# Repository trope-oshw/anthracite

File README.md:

[日本語](README.ja.md)

# Anthracite

**Schematics**
- In the browser (KiCanvas): [top](https://kicanvas.org/?repo=https%3A%2F%2Fgithub.com%2Ftrope-oshw%2Fanthracite%2Ftree%2Fmain%2Fhardware%2Ftop), [bottom](https://kicanvas.org/?repo=https%3A%2F%2Fgithub.com%2Ftrope-oshw%2Fanthracite%2Ftree%2Fmain%2Fhardware%2Fbottom), [footswitch](https://kicanvas.org/?repo=https%3A%2F%2Fgithub.com%2Ftrope-oshw%2Fanthracite%2Ftree%2Fmain%2Fhardware%2Ffootswitch)
- PNG or PDF: [`docs/schematics`](https://github.com/trope-oshw/anthracite/tree/main/docs/schematics)
- KiCad: [`hardware`](https://github.com/trope-oshw/anthracite/tree/main/hardware)

Anthracite is a MIDI-controllable analogue fuzz pedal.

It was built around the way a vintage fuzz follows the guitar's volume knob,
and to fix the parts of a fuzz pedal that are awkward to live with.

For example, you can adjust the input impedance to suit the guitar you plug in,
and MIDI control switches the pedal on and off without a loop switcher. A wah
in front of it keeps its effect. Control is digital, but the signal path is
analogue throughout.

Designed and built by [Trope](https://trope-oshw.org).
Finished, tested units are sold at [trope-oshw.org/anthracite](https://trope-oshw.org/anthracite/).

<table>
  <tr>
    <td align="center"></td>
    <td align="center"></td>
    <td align="center"></td>
  </tr>
  <tr>
    <td align="center">Angled view, LED lit</td>
    <td align="center">Top edge: MIDI IN / OUT (3.5 mm TRS) and 9 V DC</td>
    <td align="center">Input side: 1/4" jack</td>
  </tr>
</table>

Inside, with the back cover removed (v1.1)

## So what's in here:

- `hardware` has the KiCad files.
- `firmware` has the source code for the STM32 microcontroller that controls
  Anthracite.
- `enclosure` has the STEP data. The DXF for laser marking is in there too,
  with the Anthracite name and the Trope logo removed.
- `docs` has the schematics as PDF and PNG, the BOMs and so on.

The user manual, measured data and circuit explanations are published at
**https://docs.trope-oshw.org**. Apart from the main data, they are not
duplicated here.

## What kind of sound is this:

I'm not very good at playing the guitar, but this might be helpful. I switch
the guitar's volume between 10 and 6 as I play. The amp is a
[UAFX Dream '65](https://www.uaudio.com/products/dream-65-reverb-amplifier)
and the guitar is a J.W. Black S-style.

Anthracite should be played into a preamp that is already overdriven. In most
cases, putting an overdrive or distortion pedal after it may not give good
results.

## Schematics

### Top board

All of the analogue circuitry, the power-input protection, the MIDI input and
the main LED.

### Bottom board

Everything that is not on the top board: the MCU and its peripherals, the
ripple filter and negative-rail generator, the linear regulators, the MIDI
output and so on.

The hierarchical sheet in the schematic above contains the circuit below. It
is a simple level shifter that takes the analogue-switch control signals from
0 – 3.3 V to −8 – +8 V.

## Specifications

| | |
|---|---|
| Power | 9 V DC, centre-negative, 5.5 / 2.1 mm barrel. No battery operation |
| Recommended operating voltage | 8.6 – 10.0 V |
| Current draw | About **70 mA** at 9 V with the effect on |
| Adapter rating | 200 mA or more required; 500 mA recommended |
| Input impedance | About **13 kΩ** (Single) / **24 kΩ** (Hum) / **44 kΩ** (Wah) at 1 kHz, effect on |
| Input impedance, bypassed | About **1 MΩ** from 100 Hz to 1 kHz |
| Output impedance | About **1 kΩ** at 1 kHz |
| Bypass | Buffered. Switched by analogue switches |
| MIDI | 3.5 mm TRS, MIDI Type-A, 31250 baud. MIDI IN, and a MIDI OUT (Thru) jack that doubles as an external-switch input |
| Microcontroller | STM32F030C8T6 (Cortex-M0, 48 MHz, LQFP48) |
| Enclosure | 73.5 (W) × 57.5 (H) × 128 (D) mm including knobs and jacks, 268 g |

### Boards

| Board | Size | Layers | Copper |
|---|---|---|---|
| Top (analogue) | 60 × 102 mm | 4 | 35 µm (1 oz) outer, 17.5 µm (0.5 oz) inner |
| Bottom (control) | 60 × 73.5 mm | 4 | 35 µm (1 oz) outer, 17.5 µm (0.5 oz) inner |
| Footswitch | 14 × 16.15 mm | 2 | — |

All boards are 1.6 mm FR-4.

## Controls

Four potentiometers and three three-position toggles.

### Volume

Just a volume control. It does not affect the frequency response or the
distortion.

### Fuzz

Changes the gain of the fuzz circuit. The small-signal gain is shown below
(Bias: Center, Response: Gradual).

### Bass

A shelving EQ that behaves differently when cutting and when boosting: the cut
is designed to cover a wider band than the boost.

### Treble

Similar to Bass.

### Bias

Changes the operating-point ratio of the output-side transistor in the fuzz
circuit. There are four ratios: Center (1:1), Offset (2:1), Skew (3:1) and
X-Skew (4:1). X-Skew can be selected over MIDI, among other ways.
(400 Hz, Fuzz 50 %, about 0.1 Vpp in, Response: Gradual)

### Response

Steep lowers the gain and tilts the response towards the highs, which suits
rhythm playing and clean tones. Gradual has more gain and follows the guitar's
volume knob less closely, which suits overdrive-centred sounds.
(Fuzz 50 %, Bias: Center)

### Input

Gives each kind of source an input impedance that suits it. The way a vintage
fuzz follows the guitar's volume knob is available with both single coils and
humbuckers. There is also a dedicated mode that solves the usual trouble with
a wah.

## MIDI

Control Change (CC) messages received on MIDI IN switch the effect on and off
and select the mode of each toggle. As shipped, the pedal listens on
channel 12.

| CH | CC | Function | Value: 0 | 1 – 31 | 32 – 63 | 64 – 95 | 96 – 127 |
|:---:|:---:|:---:|:---:|:---:|:---:|:---:|:---:|
| **12** | **#81** | **Effect** | Bypass | Bypass | Bypass | Effect On | Effect On |
| **12** | **#83** | Input | Return (1) | Single | Hum | Wah | All-OFF (2) |
| **12** | **#84** | Response | Return (1) | Steep | Medium | Gradual | (No Assign) |
| **12** | **#85** | Bias | Return (1) | Center | Offset | Skew | X-Skew |

(1) Returns to the mode set by the toggle position. Moving the toggle on the
panel does the same; as a rule, whichever was operated last takes effect.

(2) The input filter is not applied even with the effect on, so the input
stays at the same high impedance as in bypass. Use it when, for example, there
is a buffer in front of the pedal.

With MIDI-Learn you can change the channel and the CC used for Effect.

Details are in the [user manual](https://docs.trope-oshw.org/Anthracite/) and
the [firmware](https://github.com/trope-oshw/anthracite/tree/main/firmware).

## Building the boards

The KiCad projects need KiCad 10 or later. They are self-contained: every
custom symbol and footprint is in the project's own `libs/` directory, so you
can clone this repository and open them without installing anything else.

[`hardware/parts.md`](hardware/parts.md) lists the parts chosen for each board,
with manufacturer part numbers and LCSC numbers.

Ordering parameters used for the production run are recorded in
`ordering-notes.md` attached to each release. They matter, because a different
stackup or copper weight gives a different board.

## Firmware

The full source is in [`firmware/`](firmware/). Built as described in
[firmware/README.md](firmware/README.md), it reproduces the image on shipped
units byte for byte; that file gives the toolchain versions, the SHA-256 of the
image, and how to write it to a finished unit.

You do not need to touch the firmware to use the pedal; the instructions are
there because being able to replace the software on hardware you own is part
of what this licence is for.

Firmware 1.1.0 is for v1.1 boards only, and 1.0.0 is for v1.0 boards only.
Compatibility between them is not guaranteed.

## Licensing

| What | Licence |
|---|---|
| Hardware (`hardware/`, `enclosure/`) | **CERN-OHL-S-2.0** |
| Symbols and footprints derived from the KiCad standard libraries (`hardware/*/libs/`, listed in `REUSE.toml`) | **CC-BY-SA-4.0 WITH KiCad-libraries-exception** (the symbol libraries also CERN-OHL-S-2.0) |
| Firmware (`firmware/`), except third-party code | **GPL-3.0-or-later** |
| Generated design documents (`docs/`: schematics, bills of materials, board 3D) | **CERN-OHL-S-2.0** |
| Product photographs and measured-data plots (`docs/images/`) | **CC-BY-SA-4.0** |
| Text (this README, CHANGELOG, ERRATA, CONTRIBUTING, TRADEMARK) | **CC-BY-SA-4.0** |

Full texts are in [`LICENSES/`](LICENSES/); per-file assignments are declared in
[`REUSE.toml`](REUSE.toml) following the [REUSE](https://reuse.software/)
specification. See [`COPYRIGHT.txt`](COPYRIGHT.txt) for the notices.

Code from STMicroelectronics and Arm, and symbols and footprints derived from
the KiCad standard libraries, keep their original licences. `REUSE.toml` lists
the files.

## Trademark

The design files are open source, but the names Trope, 山本回路設計 and
Anthracite, and the Trope logo, are trademarks and are not covered by the
licences above. You are free to build and sell derivatives; please give them
your own name. You may state that your product is *based on the Anthracite
design by Trope*. The published files carry no Trope branding.

Details are in [TRADEMARK.md](TRADEMARK.md). Questions, or a request to use
the marks: trope.oshw@gmail.com. Ask first, and the answer is almost always
yes.

## Versions

The product and the boards carry a `vMAJOR.MINOR` number, silkscreened on the
PCB. The firmware carries its own semantic version. They move independently:
fixing a firmware bug does not change the boards, so the board version stays put.

See [CHANGELOG.md](CHANGELOG.md) for what changed in each release, and
[ERRATA.md](ERRATA.md) for problems found in hardware that has already been
built. **If your unit behaves differently from this documentation, check the
errata first.**

## Buying one

Anthracite is on sale. Trope builds and tests each unit and ships it with its
own test report. The product page at **https://trope-oshw.org/anthracite/**
shows the current price and takes orders. Trope publishes the cost breakdown
and the formula behind the price at **https://docs.trope-oshw.org**.
Trope ships within Japan only. Questions go to trope.oshw@gmail.com.

## Contributing

Issues are welcome. As a rule, Trope does not accept pull requests to the
hardware; [CONTRIBUTING.md](CONTRIBUTING.md) explains why. Firmware and
documentation PRs are welcome.

## Disclaimer

This design is distributed **as-is, with no warranty of any kind**, express or
implied, including merchantability and fitness for a particular purpose. See
sections 6.1 and 6.2 of the CERN-OHL-S v2 for the full disclaimer.

If you build, modify, or sell hardware based on these files, **you are the
manufacturer** of that hardware. You alone are responsible for its safety and
for its compliance with every regulation that applies where you place it on the
market. Any certification, testing, or conformity marking obtained by
山本回路設計 applies **only to units built and sold by 山本回路設計**, and does
not transfer to your build.

Use a regulated, correctly-polarised 9 V DC supply. Incorrect power can damage
the pedal and whatever is connected to it.

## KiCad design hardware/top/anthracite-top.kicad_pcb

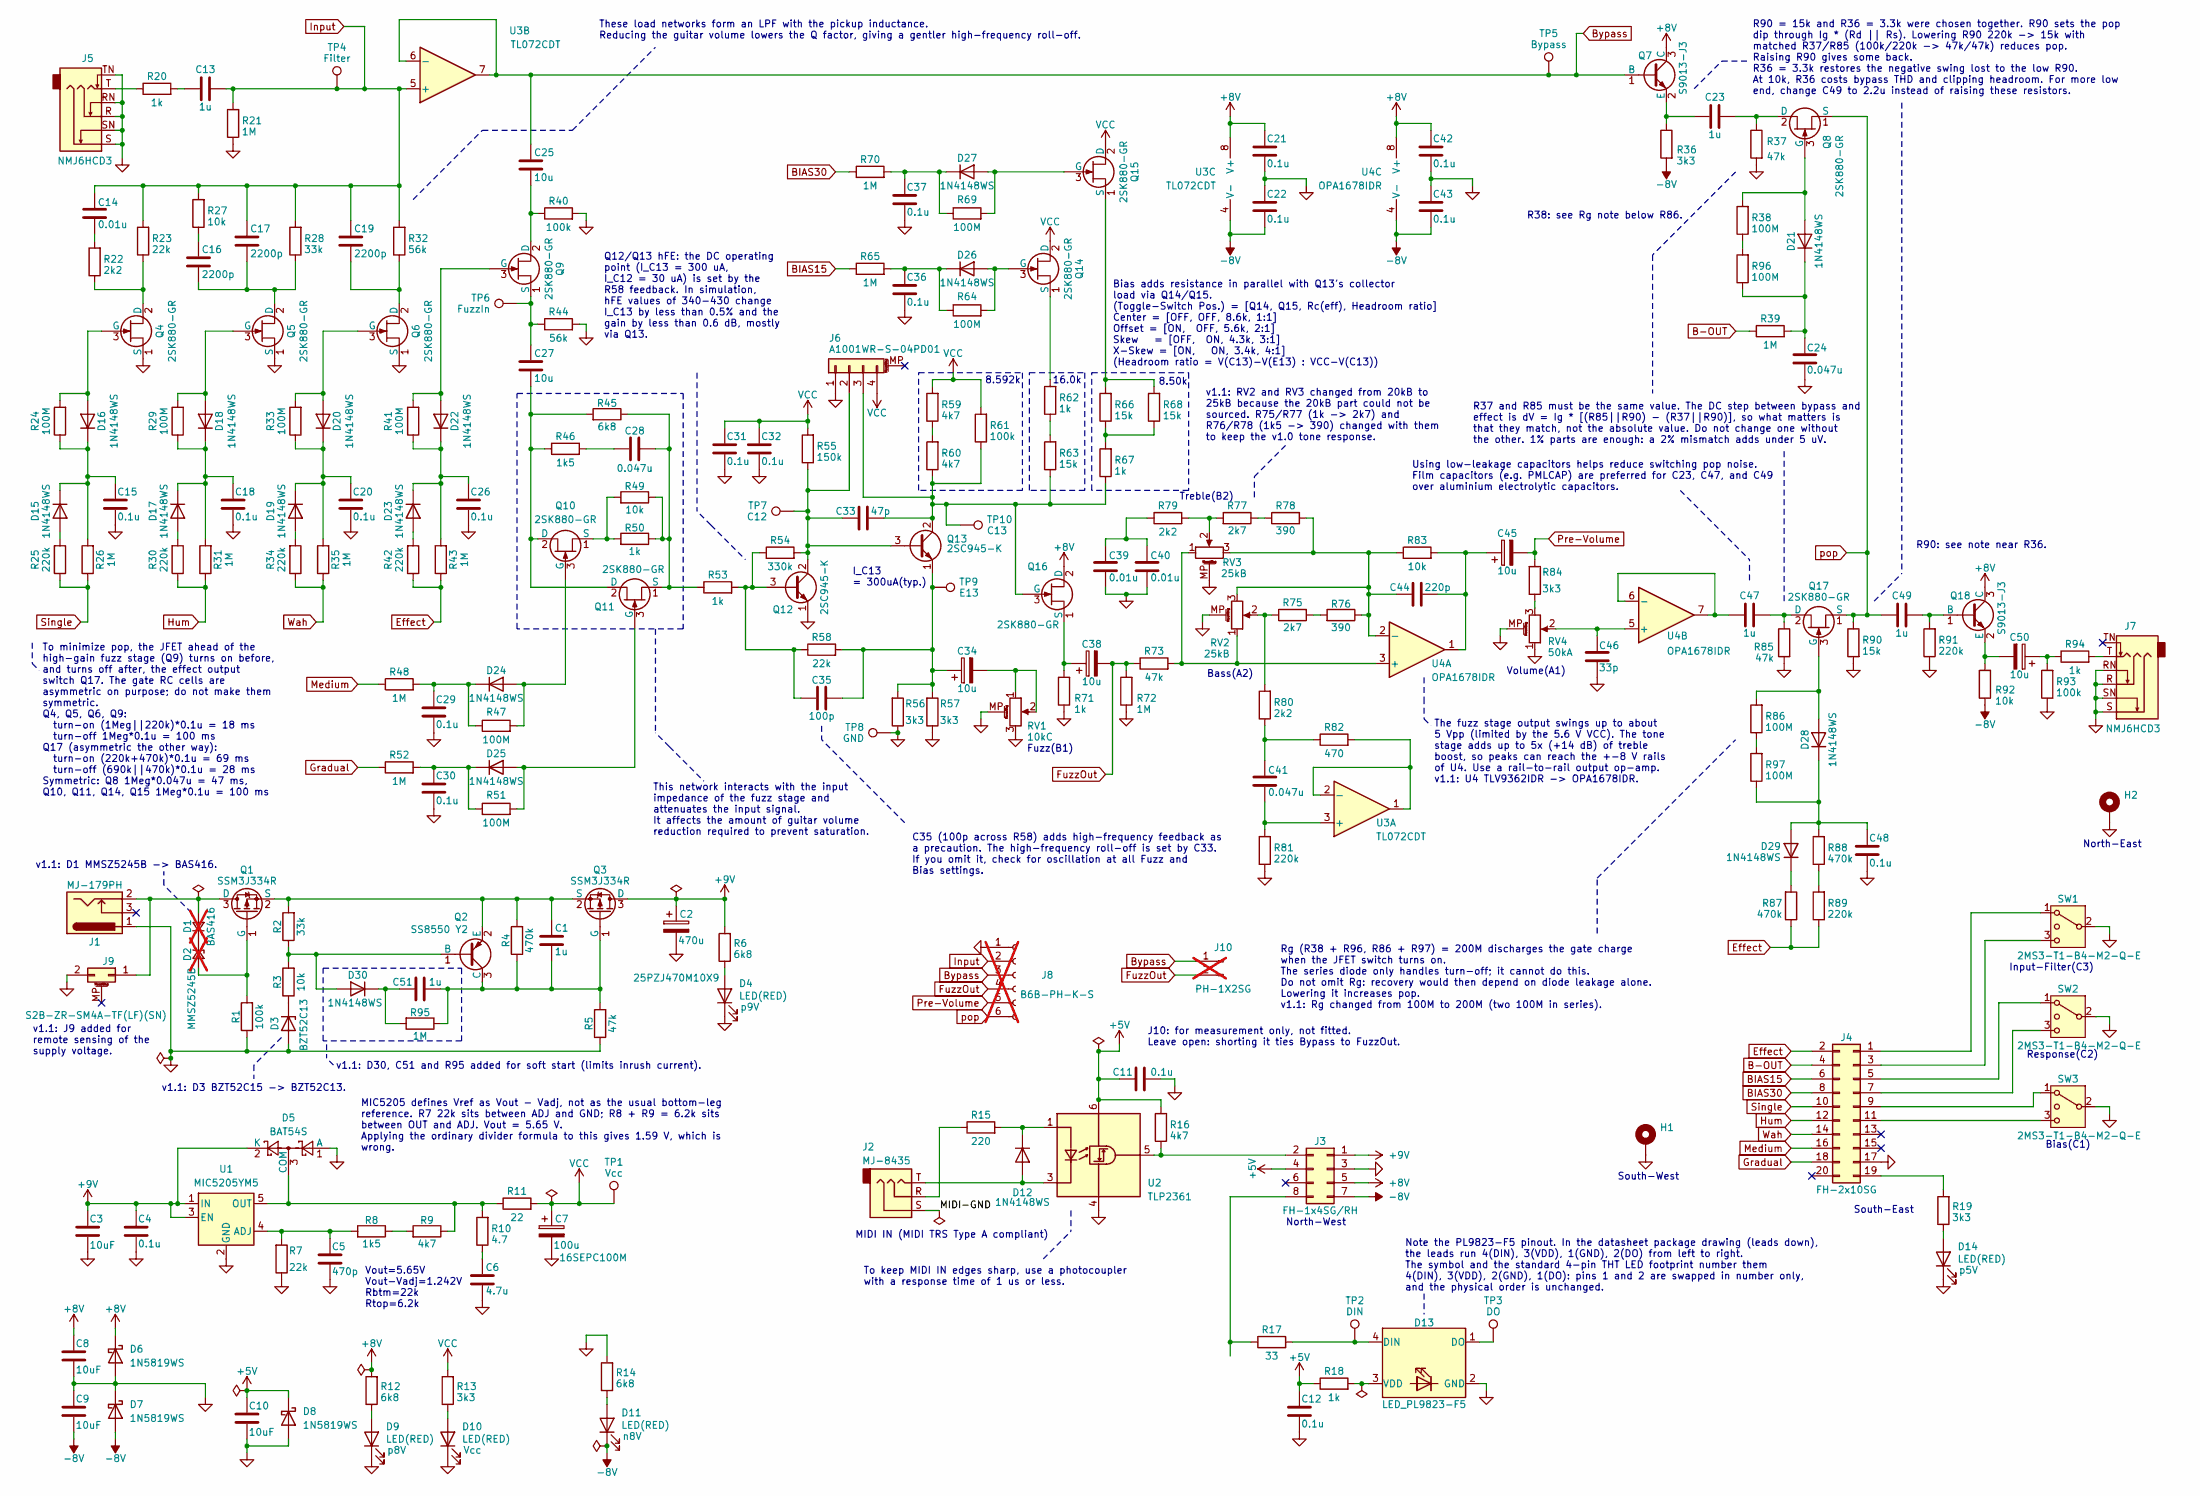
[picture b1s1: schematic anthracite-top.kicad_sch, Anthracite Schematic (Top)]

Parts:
C1, C51: 1u; C_0805_2012Metric; Tolerance 10%; Voltage 50V; MPN CL21B105KBFNNNE; LCSC C28323
C2: 470u; CP_Radial_D10.0mm_P5.00mm; Tolerance 20%; Voltage 25V; MPN 25PZJ470M10X9
C3, C8, C9, C10: 10uF; C_0805_2012Metric; Tolerance 10%; Voltage 25V; MPN CL21A106KAYNNNE; LCSC C15850
C4, C11, C12, C15, C18, C20, C21, C22, C26, C29, C30, C31, C32, C36, C37, C42, C43, C48: 0.1u; C_0603_1608Metric; Tolerance 10%; Voltage 50V; LCSC C14663
C5: 470p; C_0603_1608Metric; Tolerance 10%; Voltage 50V; LCSC C1620
C6: 4.7u; C_0805_2012Metric; Tolerance 10%; Voltage 25V; LCSC C1779
C7: 100u; CP_Radial_D6.3mm_P2.50mm; Tolerance 20%; Voltage 16V; MPN 16SEPC100M
C13, C23, C47, C49: 1u; C_1206_3216Metric_Pad1.33x1.80mm_HandSolder; Tolerance 20%; Voltage 25V; MPN 25MU105MA23216; LCSC C3776619
C14, C39, C40: 0.01u; C_0603_1608Metric; Tolerance 5%; Voltage 50V; MPN GRM1885C1H103JA01D; LCSC C85973
C16, C17, C19: 2200p; C_0805_2012Metric; Tolerance 5%; Voltage 50V; LCSC C28260
C24: 0.047u; C_0805_2012Metric; Tolerance 10%; Voltage 50V; LCSC C53134
C25, C27: 10u; C_1812_4532Metric_Pad1.57x3.40mm_HandSolder; Tolerance 20%; Voltage 16V; MPN 16MU106MC44532
C28, C41: 0.047u; C_1206_3216Metric_Pad1.33x1.80mm_HandSolder; Tolerance 5%; Voltage 50V; MPN GRM31M5C1H473JA01L; LCSC C21812
C33: 47p; C_0603_1608Metric; Tolerance 5%; Voltage 50V; LCSC C1671
C34, C38, C45, C50: 10u; CP_Elec_4x5.4; Tolerance 20%; Voltage 16V; MPN EEE1CA100SR; LCSC C178496
C35: 100p; C_0603_1608Metric; Tolerance 5%; Voltage 50V; MPN CL10C101JB8NNNC; LCSC C14858
C44: 220p; C_0603_1608Metric; Tolerance 10%; Voltage 50V; LCSC C1603
C46: 33p; C_0603_1608Metric; Tolerance 5%; Voltage 50V; LCSC C1663
D1: BAS416; D_SOD-323; MPN BAS416; LCSC C7502719; not fitted
D2: MMSZ5245B; D_SOD-123; MPN MMSZ5245B; LCSC C19077428; not fitted
D3: BZT52C13; D_SOD-123; MPN BZT52C13; LCSC C19077411
D4, D9, D10, D11, D14: LED(RED); D_0603_1608Metric_Name; MPN KT-0603R; LCSC C2286
D5: BAT54S; SOT-23; MPN BAT54S; LCSC C7420333
D6, D7, D8: 1N5819WS; D_SOD-323; MPN 1N5819WS; LCSC C191023
D12, D15, D16, D17, D18, D19, D20, D21, D22, D23, D24, D25, D26, D27, D28, D29, D30: 1N4148WS; D_SOD-323; MPN 1N4148WS; LCSC C2128
D13: LED_PL9823-F5; LED_D5.0mm-4_RGB_Wide_Pins; MPN PL9823-F5
H1, H2: MountingHole_Pad; MountingHole_3.2mm_M3_DIN965_Pad
J1: MJ-179PH; MJ-179PH_Edge; MPN MJ-179PH
J2: MJ-8435; MPN MJ-8435
J3: FH-1x4SG/RH; PinSocket_2x04_P2.54mm_Vertical; MPN FH-1x4SG/RH x2
J4: FH-2x10SG; PinSocket_2x10_P2.54mm_Vertical; MPN FH-2x10SG
J5, J7: NMJ6HCD3; Jack_6.35mm_Neutrik_NMJ6HCD3_Horizontal; MPN NMJ6HCD3
J6: A1001WR-S-04PD01; JST_SH_SM04B-SRSS-TB_1x04-1MP_P1.00mm_Horizontal; MPN A1001WR-S-04PD01; LCSC C371571
J8: B6B-PH-K-S; JST_PH_B6B-PH-K_1x06_P2.00mm_Vertical; MPN B6B-PH-K-S(LF)(SN); not fitted
J9: S2B-ZR-SM4A-TF(LF)(SN); JST_ZH_S2B-ZR-SM4A-TF_1x02-1MP_P1.50mm_Horizontal; MPN S2B-ZR-SM4A-TF(LF)(SN); LCSC C265329
J10: PH-1X2SG; PinHeader_1x02_P2.54mm_Vertical; MPN PH-1X2SG; not fitted
Q1, Q3: SSM3J334R; SOT-23; MPN SSM3J334R; LCSC C396017
Q2: SS8550 Y2; SOT-23; MPN SS8550 Y2(RANGE:200-350); LCSC C8542
Q4, Q5, Q6, Q8, Q9, Q10, Q11, Q14, Q15, Q16, Q17: 2SK880-GR; SOT-323_SC-70; MPN 2SK880-GR; LCSC C7469759
Q7, Q18: S9013-J3; SOT-23; MPN S9013 J3(RANGE:200-350); LCSC C6749
Q12, Q13: 2SC945-K; TO-92_Inline_Wide; MPN 2SC945-K
R1, R40, R61, R93: 100k; R_0603_1608Metric; Tolerance 1%; LCSC C25803
R2, R28: 33k; R_0603_1608Metric; Tolerance 1%; LCSC C4216
R3, R27, R49, R83, R92: 10k; R_0603_1608Metric; Tolerance 1%; LCSC C25804
R4, R87, R88: 470k; R_0603_1608Metric; Tolerance 1%; LCSC C23178
R5, R37, R73, R85: 47k; R_0603_1608Metric; Tolerance 1%; LCSC C25819
R6, R12, R14, R45: 6k8; R_0603_1608Metric; Tolerance 1%; LCSC C23212
R7, R23, R58: 22k; R_0603_1608Metric; Tolerance 1%; LCSC C31850
R8, R46: 1k5; R_0603_1608Metric; Tolerance 1%; LCSC C22843
R9, R16, R59, R60: 4k7; R_0603_1608Metric; Tolerance 1%; LCSC C23162
R10: 4.7; R_0603_1608Metric; Tolerance 1%; LCSC C23164
R11: 22; R_0603_1608Metric; Tolerance 1%; LCSC C23345
R13, R19, R36, R56, R57, R84: 3k3; R_0603_1608Metric; Tolerance 1%; LCSC C22978
R15: 220; R_0603_1608Metric; Tolerance 1%; LCSC C22962
R17: 33; R_0603_1608Metric; Tolerance 1%; LCSC C23140
R18, R20, R50, R53, R62, R67, R71, R94: 1k; R_0603_1608Metric; Tolerance 1%; LCSC C21190
R21, R26, R31, R35, R39, R43, R48, R52, R65, R70, R72: 1M; R_0603_1608Metric; Tolerance 1%; LCSC C22935
R22, R79, R80: 2k2; R_0603_1608Metric; Tolerance 1%; LCSC C4190
R24, R29, R33, R38, R41, R47, R51, R64, R69, R86, R96, R97: 100M; R_0603_1608Metric; Tolerance 5%; LCSC C422892
R25, R30, R34, R42, R81, R89, R91: 220k; R_0603_1608Metric; Tolerance 1%; LCSC C22961
R32, R44: 56k; R_0603_1608Metric; Tolerance 1%; LCSC C23206
R54: 330k; R_0603_1608Metric; Tolerance 1%; LCSC C23137
R55: 150k; R_0603_1608Metric; Tolerance 1%; LCSC C22807
R63, R66, R68, R90: 15k; R_0603_1608Metric; Tolerance 1%; LCSC C22809
R75, R77: 2k7; R_0603_1608Metric; Tolerance 1%; LCSC C13167
R76, R78: 390; R_0603_1608Metric; Tolerance 1%; LCSC C23151
R82: 470; R_0603_1608Metric; Tolerance 1%; LCSC C23179
R95: 1M; R_0402_1005Metric; Tolerance 1%; LCSC C26083
RV1: 10kC; Potentiometer_Alpha_RD901F-40-00D_Single_Vertical_CenterAnk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; MPN RD901F-40-15R1-C10K
RV2, RV3: 25kB; Potentiometer_Alpha_RD901F-40-00D_Single_Vertical_CenterAnk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; MPN RD901F-40-15R1-B25K
RV4: 50kA; Potentiometer_Alpha_RD901F-40-00D_Single_Vertical_CenterAnk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; MPN RD901F-40-15R1-A50K
SW1, SW2, SW3: 2MS3-T1-B4-M2-Q-E; Toggle_SW_mini_2MS1-T1-B4-M2-Q-E; MPN 2MS3-T1-B4-M2-Q-E
TP1, TP2, TP3, TP4, TP5, TP6, TP7, TP8, TP9, TP10: TestPoint; TestPoint_Pad_1.5x1.5mm_Label
U1: MIC5205YM5; SOT-23-5; MPN MIC5205YM5; LCSC C412820
U2: TLP2361; SO-5-6_4.55x3.7mm_P1.27mm; MPN TLP2361(TPL,E; LCSC C107626
U3: TL072CDT; SOIC-8_3.9x4.9mm_P1.27mm; MPN TL072CDT; LCSC C6961
U4: OPA1678IDR; SOIC-8_3.9x4.9mm_P1.27mm; MPN OPA1678IDR; LCSC C192421

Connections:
+5V: C10.1, C11.1, C12.1, D8.1 (K), J3.4, R16.2, R18.1, U2.6 (VDD)
+8V: C8.1, C21.1, C42.1, D6.1 (K), J3.5, Q7.3 (C), Q16.2 (D), Q18.3 (C), R12.2, U3.8 (V+), U4.8 (V+)
+9V: C2.1, C3.1, C4.1, D5.2 (K), J3.1, Q3.3 (D), R6.2, U1.1 (IN), U1.3 (EN)
-8V: C9.2, C22.2, C43.2, D7.2 (A), D11.1 (K), J3.7, R36.1, R92.1, U3.4 (V-), U4.4 (V-)
/MIDI-GND: J2.S
B-OUT: J4.4, R39.1
BIAS15: J4.6, R65.1
BIAS30: J4.8, R70.1
Bypass: C25.2, J8.3, J10.1, Q7.1 (B), TP5.1 (1_1), U3.6 (-), U3.7
Effect: J4.2, R42.1, R43.1, R87.1, R89.1
FuzzOut: C38.2, J8.4, J10.2, R72.2, R73.1
GNDPWR: C2.2, C3.2, C4.2, C5.2, C6.2, C7.2, C8.2, C9.1, C10.2, C11.2, C12.2, C15.2, C18.2, C20.2, C21.2, C22.1, C24.1, C26.2, C29.2, C30.2, C31.2, C32.2, C36.2, C37.2, C39.2, C40.2, C42.2, C43.1, C46.2, C48.2, D3.2 (A), D4.1 (K), D5.1 (A), D6.2 (A), D7.1 (K), D8.2 (A), D9.1 (K), D10.1 (K), D13.2 (GND), D14.1 (K), H1.1 (1_1), H2.1 (1_1), J1.1, J3.3, J4.17, J5.R, J5.RN, J5.S, J5.SN, J5.TN, J6.1, J7.R, J7.RN, J7.S, J7.SN, J8.1, J9.2, Q4.1 (S), Q5.1 (S), Q6.1 (S), Q12.1 (E), R1.1, R5.1, R7.2, R14.2, R21.1, R37.1, R40.2, R44.2, R56.2, R57.2, R71.1, R72.1, R81.1, R85.1, R90.1, R91.1, R93.1, RV1.3, RV1.MP (MountPin), RV2.MP (MountPin), RV3.MP (MountPin), RV4.1, RV4.MP (MountPin), SW1.2 (3), SW2.2 (3), SW3.2 (3), TP8.1 (1_1), U1.2 (GND), U2.4 (GND)
Gradual: J4.18, R52.1
Hum: J4.12, R30.1, R31.1
Input: C13.2, C14.1, C17.1, C19.1, J8.2, R21.2, R23.2, R27.2, R28.2, R32.2, TP4.1 (1_1), U3.5 (+)
Medium: J4.16, R48.1
unnamed: C6.1, R10.1
unnamed: C13.1, R20.2
unnamed: C14.2, R22.2
unnamed: C16.1, R27.1
unnamed: C28.1, R46.2
unnamed: C34.2, RV1.1, RV1.2
unnamed: C39.1, C40.1, R79.1
unnamed: C41.1, R80.1, R82.1
unnamed: C44.2, C45.1, R83.2, U4.1
unnamed: C50.1, R93.2, R94.1
unnamed: D1.2 (A), J1.2, J9.1, Q1.3 (D)
unnamed: D1.1 (K), D2.1 (K)
unnamed: D2.2 (A), Q1.1 (G), R1.2
unnamed: D3.1 (K), R3.1
unnamed: D4.2 (A), R6.1
unnamed: D5.3 (COM), R9.2, R10.2, R11.1, U1.5 (OUT)
unnamed: D9.2 (A), R12.1
unnamed: D10.2 (A), R13.1
unnamed: D11.2 (A), R14.1
unnamed: D12.2 (A), J2.T, U2.3 (K)
unnamed: D12.1 (K), R15.2, U2.1 (A)
unnamed: D13.4 (DIN), R17.2, TP2.1 (1_1)
unnamed: D13.1 (DO), TP3.1 (1_1)
unnamed: D13.3 (VDD), R18.2
unnamed: D14.2 (A), R19.1
unnamed: D15.2 (A), R25.2
unnamed: C15.1, D15.1 (K), D16.1 (K), R24.1, R26.2
unnamed: D16.2 (A), Q4.3 (G), R24.2
unnamed: D17.2 (A), R30.2
unnamed: C18.1, D17.1 (K), D18.1 (K), R29.1, R31.2
unnamed: D18.2 (A), Q5.3 (G), R29.2
unnamed: D19.2 (A), R34.2
unnamed: C20.1, D19.1 (K), D20.1 (K), R33.1, R35.2
unnamed: D20.2 (A), Q6.3 (G), R33.2
unnamed: D21.2 (A), Q8.3 (G), R38.2
unnamed: C24.2, D21.1 (K), R39.2, R96.1
unnamed: D22.2 (A), Q9.3 (G), R41.2
unnamed: C26.1, D22.1 (K), D23.1 (K), R41.1, R43.2
unnamed: D23.2 (A), R42.2
unnamed: D24.2 (A), Q10.3 (G), R47.2
unnamed: C29.1, D24.1 (K), R47.1, R48.2
unnamed: D25.2 (A), Q11.3 (G), R51.2
unnamed: C30.1, D25.1 (K), R51.1, R52.2
unnamed: D26.2 (A), Q14.3 (G), R64.2
unnamed: C36.1, D26.1 (K), R64.1, R65.2
unnamed: D27.2 (A), Q15.3 (G), R69.2
unnamed: C37.1, D27.1 (K), R69.1, R70.2
unnamed: D28.2 (A), Q17.3 (G), R86.2
unnamed: C48.1, D28.1 (K), D29.2 (A), R88.2, R97.1
unnamed: D29.1 (K), R87.2
unnamed: D30.2 (A), Q2.1 (B), R2.1, R3.2
unnamed: C51.1, D30.1 (K), R95.1
unnamed: J2.R, R15.1
unnamed: J3.2, R16.1, U2.5 (VO)
unnamed: J3.8, R17.1
unnamed: J4.1, SW1.1
unnamed: J4.3, SW1.3 (4)
unnamed: J4.5, SW2.1
unnamed: J4.7, SW2.3 (4)
unnamed: J4.9, SW3.1
unnamed: J4.11, SW3.3 (4)
unnamed: J4.19, R19.2
unnamed: J5.T, R20.1
unnamed: C33.1, J6.2, Q12.2 (C), Q13.3 (B), R54.2, R55.1, TP7.1 (1_1)
unnamed: C33.2, J6.3, Q13.2 (C), Q16.3 (G), R60.1, R61.1, R63.1, R67.1, TP10.1 (1_1)
unnamed: J7.T, R94.2
unnamed: C1.1, Q1.2 (S), Q2.2 (E), Q3.2 (S), R2.2, R4.2
unnamed: C1.2, C51.2, Q2.3 (C), Q3.1 (G), R4.1, R5.2, R95.2
unnamed: Q4.2 (D), R22.1, R23.1
unnamed: C16.2, C17.2, Q5.2 (D), R28.1
unnamed: C19.2, Q6.2 (D), R32.1
unnamed: C23.1, Q7.2 (E), R36.2
unnamed: C23.2, Q8.2 (D), R37.2
unnamed: C25.1, Q9.2 (D), R40.1
unnamed: C27.2, Q9.1 (S), R44.1, TP6.1 (1_1)
unnamed: C27.1, Q10.2 (D), Q11.2 (D), R45.1, R46.1
unnamed: Q10.1 (S), R49.1, R50.1
unnamed: C28.2, Q11.1 (S), R45.2, R49.2, R50.2, R53.1
unnamed: C35.1, Q12.3 (B), R53.2, R54.1, R58.1
unnamed: C34.1, C35.2, Q13.1 (E), R56.1, R57.1, R58.2, TP9.1 (1_1)
unnamed: Q14.1 (S), R62.2
unnamed: Q15.1 (S), R66.2, R68.2
unnamed: C38.1, Q16.1 (S), R71.2
unnamed: C47.2, Q17.2 (D), R85.2
unnamed: C49.2, Q18.1 (B), R91.2
unnamed: C50.2, Q18.2 (E), R92.2
unnamed: R8.2, R9.1
unnamed: R38.1, R96.2
unnamed: R59.1, R60.2
unnamed: R62.1, R63.2
unnamed: R66.1, R67.2, R68.1
unnamed: R75.1, R76.1
unnamed: R75.2, R80.2, RV2.2
unnamed: R77.1, R79.2, RV3.2
unnamed: R77.2, R78.2
unnamed: R84.2, RV4.3
unnamed: R86.1, R97.2
unnamed: R88.1, R89.2
unnamed: C5.1, R7.1, R8.1, U1.4 (ADJ)
unnamed: C41.2, R81.2, U3.3 (+)
unnamed: R82.2, U3.1, U3.2 (-)
unnamed: R73.2, RV2.1, RV3.1, U4.3 (+)
unnamed: C44.1, R76.2, R78.1, R83.1, RV2.3, RV3.3, U4.2 (-)
unnamed: C46.1, RV4.2, U4.5 (+)
unnamed: C47.1, U4.6 (-), U4.7
Pre-Volume: C45.2, J8.5, R84.1
Single: J4.10, R25.1, R26.1
VCC: C7.1, C31.1, C32.1, J6.4, Q14.2 (D), Q15.2 (D), R11.2, R13.2, R55.2, R59.2, R61.2, TP1.1 (1_1)
Wah: J4.14, R34.1, R35.1
pop: C49.1, J8.6, Q8.1 (S), Q17.1 (S), R90.2

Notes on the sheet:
This network interacts with the input impedance of the fuzz stage and attenuates the input signal. It affects the amount of guitar volume reduction required to prevent saturation.
MIDI IN (MIDI TRS Type A compliant)
Rg (R38 + R96, R86 + R97) = 200M discharges the gate charge when the JFET switch turns on. The series diode only handles turn-off; it cannot do this. Do not omit Rg: recovery would then depend on diode leakage alone. Lowering it increases pop. v1.1: Rg changed from 100M to 200M (two 100M in series).
South-West
v1.1: D30, C51 and R95 added for soft start (limits inrush current).
The fuzz stage output swings up to about 5 Vpp (limited by the 5.6 V VCC). The tone stage adds up to 5x (+14 dB) of treble boost, so peaks can reach the +-8 V rails of U4. Use a rail-to-rail output op-amp. v1.1: U4 TLV9362IDR -> OPA1678IDR.
Q12/Q13 hFE: the DC operating point (I_C13 = 300 uA, I_C12 = 30 uA) is set by the R58 feedback. In simulation, hFE values of 340-430 change I_C13 by less than 0.5% and the gain by less than 0.6 dB, mostly via Q13.
Bass(A2)
South-East
Using low-leakage capacitors helps reduce switching pop noise. Film capacitors (e.g. PMLCAP) are preferred for C23, C47, and C49 over aluminium electrolytic capacitors.
MIC5205 defines Vref as Vout - Vadj, not as the usual bottom-leg reference. R7 22k sits between ADJ and GND; R8 + R9 = 6.2k sits between OUT and ADJ. Vout = 5.65 V. Applying the ordinary divider formula to this gives 1.59 V, which is wrong.
Fuzz(B1)
These load networks form an LPF with the pickup inductance. Reducing the guitar volume lowers the Q factor, giving a gentler high-frequency roll-off.
R37 and R85 must be the same value. The DC step between bypass and effect is dV = Ig * [(R85||R90) - (R37||R90)], so what matters is that they match, not the absolute value. Do not change one without the other. 1% parts are enough: a 2% mismatch adds under 5 uV.
Response(C2)
To minimize pop, the JFET ahead of the high-gain fuzz stage (Q9) turns on before, and turns off after, the effect output switch Q17. The gate RC cells are asymmetric on purpose; do not make them symmetric. Q4, Q5, Q6, Q9: turn-on (1Meg||220k)*0.1u = 18 ms turn-off 1Meg*0.1u = 100 ms Q17 (asymmetric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
Vout=5.65V Vout-Vadj=1.242V Rbtm=22k Rtop=6.2k
I_C13 = 300uA(typ.)
v1.1: D1 MMSZ5245B -> BAS416.
C35 (100p across R58) adds high-frequency feedback as a precaution. The high-frequency roll-off is set by C33. If you omit it, check for oscillation at all Fuzz and Bias settings.
Note the PL9823-F5 pinout. In the datasheet package drawing (leads down), the leads run 4(DIN), 3(VDD), 1(GND), 2(DO) from left to right. The symbol and the standard 4-pin THT LED footprint number them 4(DIN), 3(VDD), 2(GND), 1(DO): pins 1 and 2 are swapped in number only, and the physical order is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
North-East
R90 = 15k and R36 = 3.3k were chosen together. R90 sets the pop dip through Ig * (Rd || Rs). Lowering R90 220k -> 15k with matched R37/R85 (100k/220k -> 47k/47k) reduces pop. Raising R90 gives some back. R36 = 3.3k restores the negative swing lost to the low R90. At 10k, R36 costs bypass THD and cl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
Input-Filter(C3)
To keep MIDI IN edges sharp, use a photocoupler with a response time of 1 us or less.
North-West
Bias adds resistance in parallel with Q13's collector load via Q14/Q15. (Toggle-Switch Pos.) = [Q14, Q15, Rc(eff), Headroom ratio] Center = [OFF, OFF, 8.6k, 1:1] Offset = [ON, OFF, 5.6k, 2:1] Skew = [OFF, ON, 4.3k, 3:1] X-Skew = [ON, ON, 3.4k, 4:1] (Headroom ratio = V(C13)-V(E13) : VCC-V(C13))
v1.1: J9 added for remote sensing of the supply voltage.
Bias(C1)
Volume(A1)
R90: see note near R36.
J10: for measurement only, not fitted. Leave open: shorting it ties Bypass to FuzzOut.
8.50k
R38: see Rg note below R86.
v1.1: RV2 and RV3 changed from 20kB to 25kB because the 20kB part could not be sourced. R75/R77 (1k -> 2k7) and R76/R78 (1k5 -> 390) changed with them to keep the v1.0 tone response.
v1.1: D3 BZT52C15 -> BZT52C13.
8.592k
Treble(B2)
16.0k

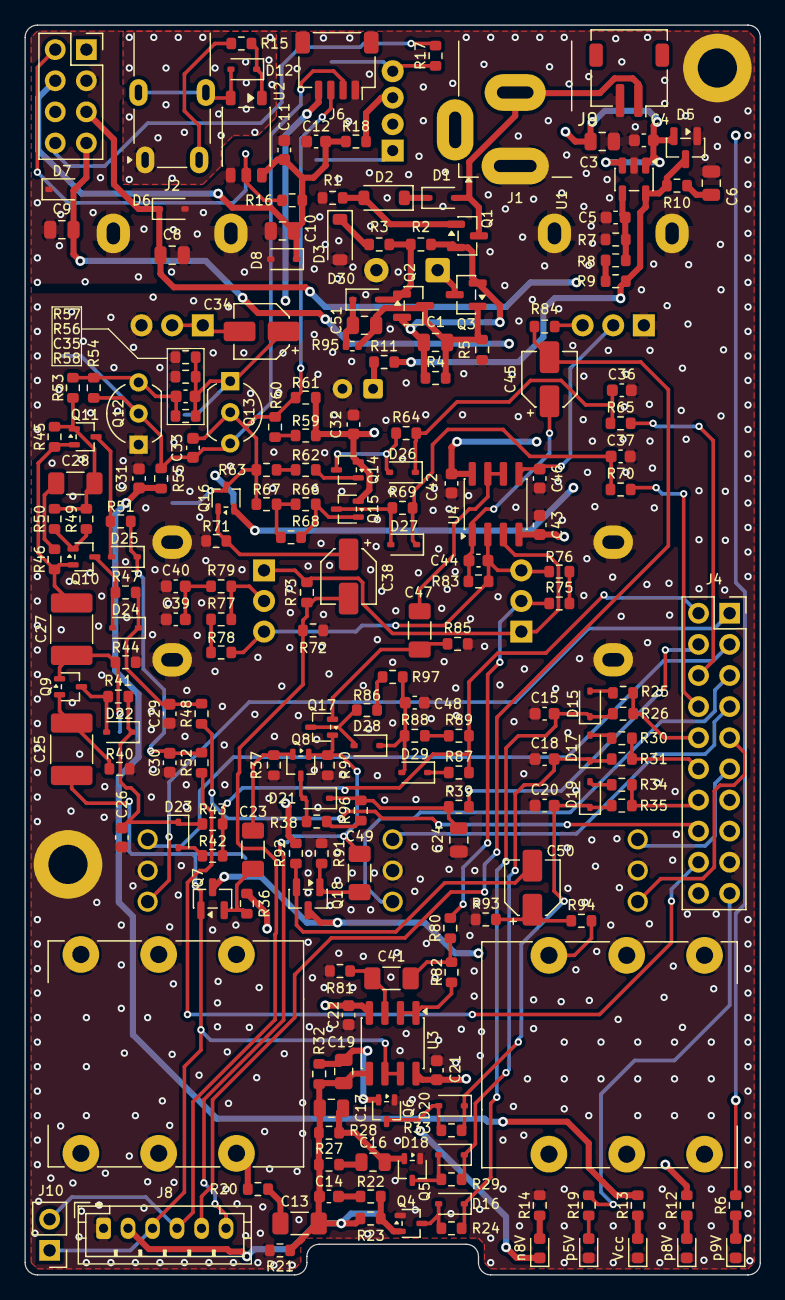
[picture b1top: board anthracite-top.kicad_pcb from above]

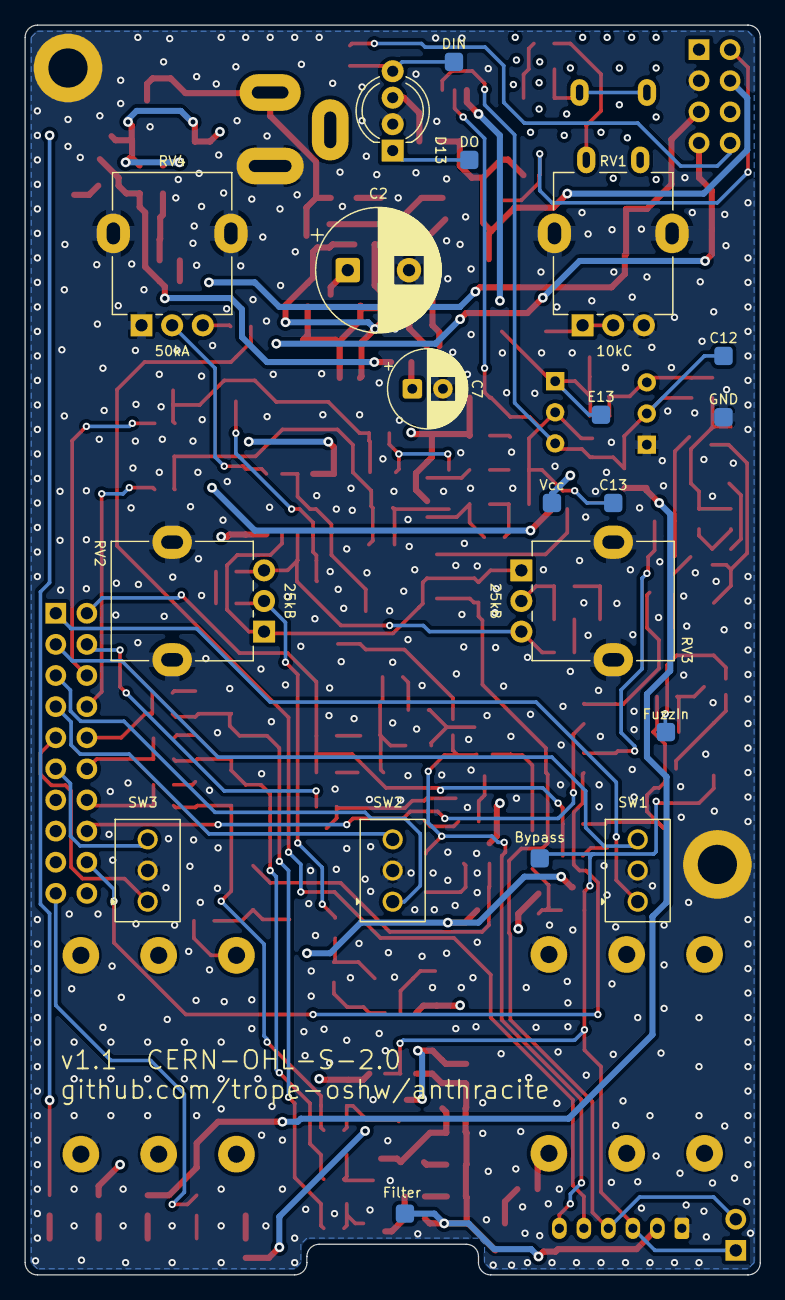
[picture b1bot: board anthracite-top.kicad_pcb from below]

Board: 4 copper layers, 60.0 x 102.0 mm, 228 parts (20 on the bottom side), 125 nets.

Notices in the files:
firmware/Src/main.c:
SPDX-FileCopyrightText: 2026 Hayata Yamamoto (Yamamoto Circuit Design)
SPDX-License-Identifier: GPL-3.0-or-later
Copyright (c) 2026 STMicroelectronics, licensed under BSD-3-Clause.
under the terms of the GNU General Public License as published by the
Free Software Foundation, either version 3 of the License, or (at your
hardware/bottom/anthracite-bottom.kicad_pcb:
Copyright 2026 Hayata Yamamoto
Licensed under CERN-OHL-S v2
${REVISION}  CERN-OHL-S-2.0
